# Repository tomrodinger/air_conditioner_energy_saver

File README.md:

# air_conditioner_energy_saver
This are all the open sources for a device that automatically controls your AC unit to turn it on or off

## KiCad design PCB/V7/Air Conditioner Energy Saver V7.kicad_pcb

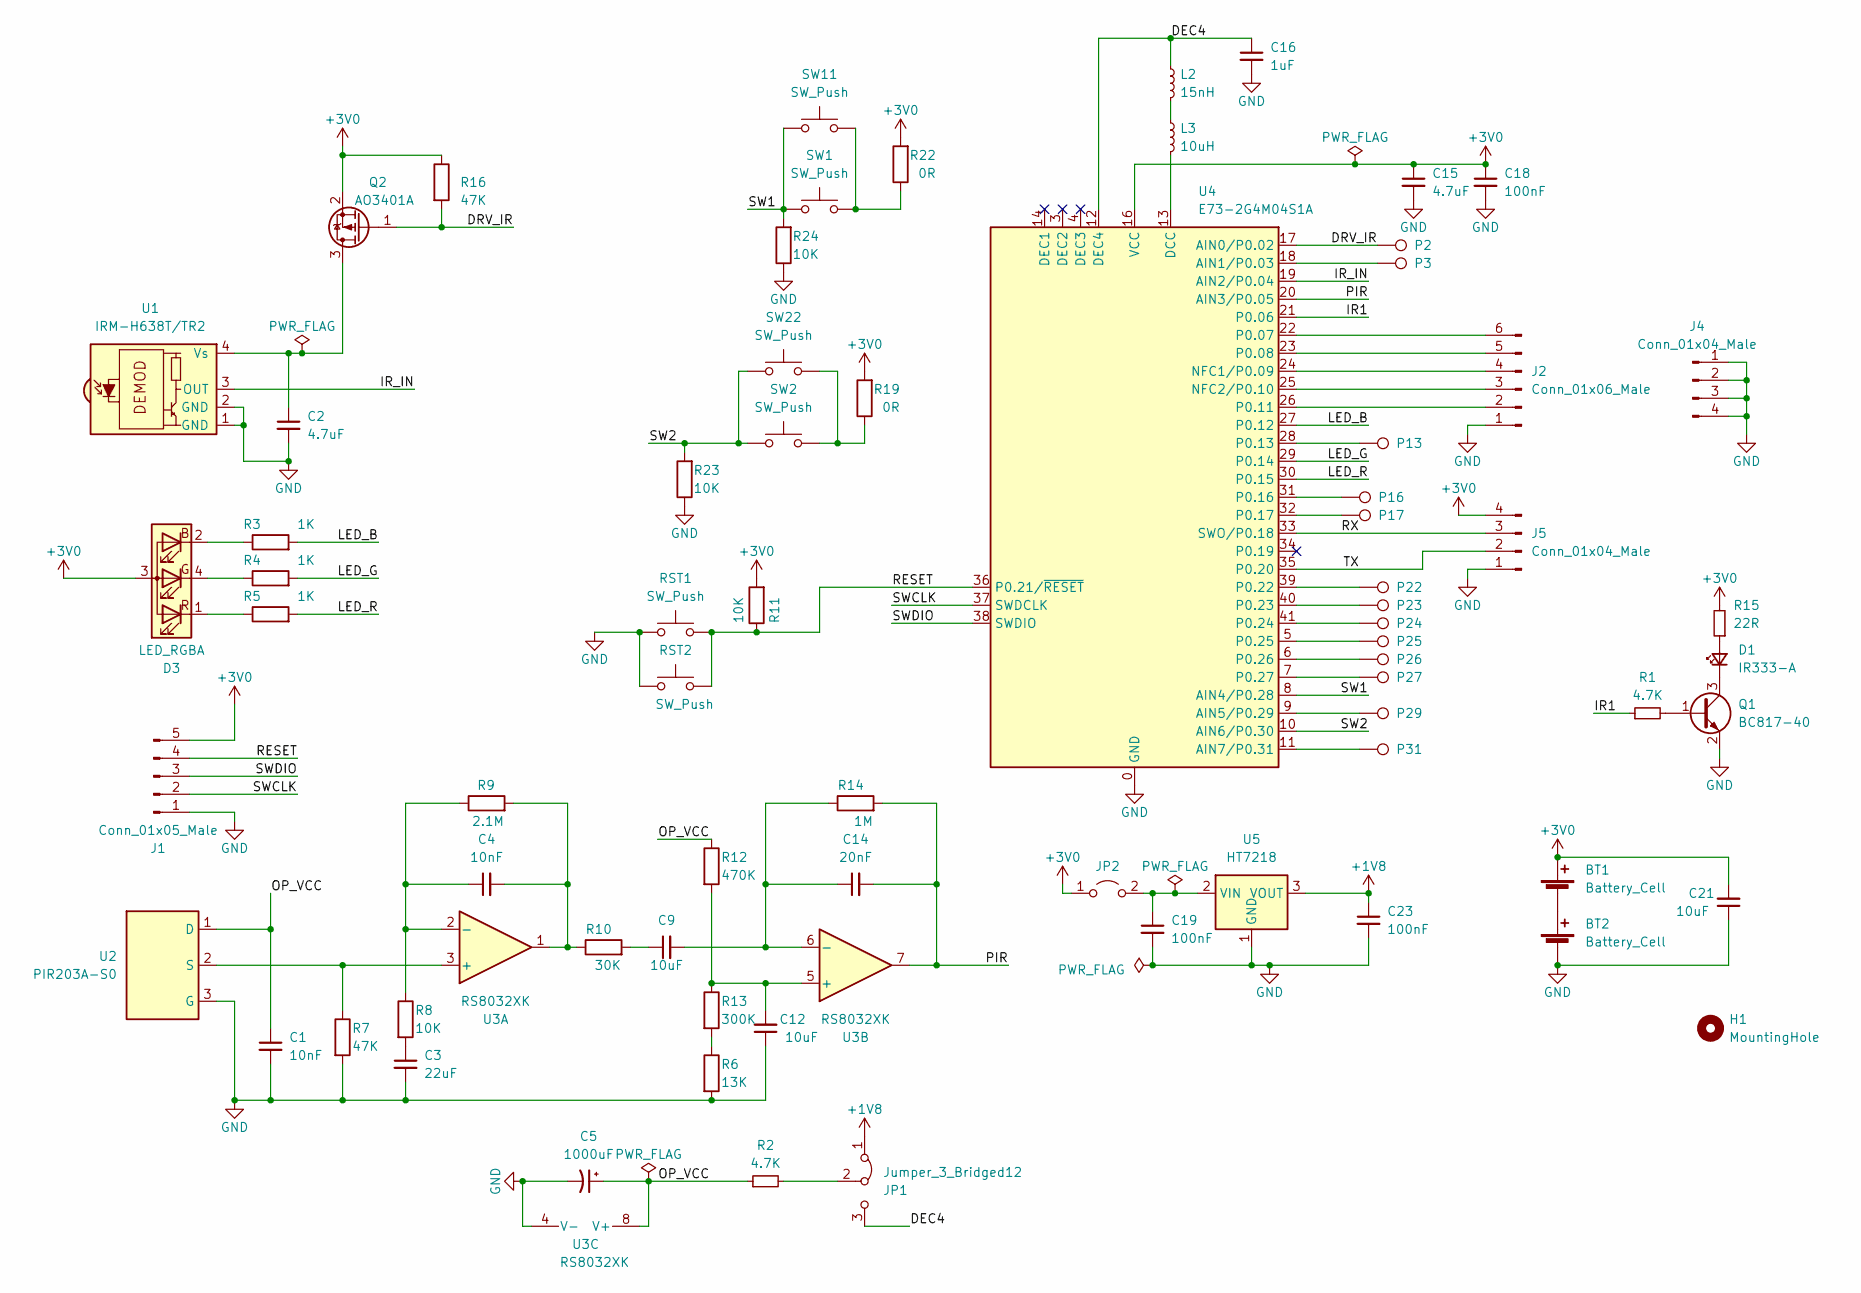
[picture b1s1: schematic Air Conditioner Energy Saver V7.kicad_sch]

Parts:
BT1, BT2: Battery_Cell; AA Batt
C1, C4: 10nF; C_0402_1005Metric; MPN CL05B103KB5NNNC; LCSC C15195
C2: 4.7uF; C_0603_1608Metric; MPN CL10A475KO8NNNC; LCSC C19666
C3: 22uF; C_1206_3216Metric; MPN CL31A226KAHNNNE; LCSC C12891
C5: 1000uF; CP_Elec_8x10.5; MPN RVT1A102M0810; LCSC C99833
C9, C12, C21: 10uF; C_1206_3216Metric; MPN CL31A106KBHNNNE; LCSC C13585
C14: 20nF; C_0603_1608Metric; MPN CC0603KRX7R9BB203; LCSC C282065
C15: 4.7uF; C_0805_2012Metric; MPN CL21A475KAQNNNE; LCSC C1779
C16: 1uF; C_0603_1608Metric; MPN CL10A105KB8NNNC; LCSC C15849
C18, C19, C23: 100nF; C_0402_1005Metric; MPN CL05B104KB54PNC; LCSC C307331
D1: IR333-A; LED_D5.0mm_Horizontal_O3.81mm_Z3.0mm; MPN IR333-A; LCSC C264290
D3: LED_RGBA; FM-B2020RGBA-HG; MPN FM-B2020RGBA-HG; LCSC PN C108793
H1: MountingHole; Mounting Hole 2.3mm
J1: Conn_01x05_Male; PinHeader_1x05_P2.54mm_Vertical; MPN PZ254V-11-05P; LCSC C492404
J2: Conn_01x06_Male; PinHeader_1x06_P2.54mm_Vertical; MPN PZ254V-11-06P; LCSC C492405
J4, J5: Conn_01x04_Male; PinHeader_1x04_P2.54mm_Vertical; MPN PZ254V-11-04P; LCSC C2691448
JP1: Jumper_3_Bridged12; PinHeader_1x03_P2.54mm_Vertical; MPN PZ254V-11-03P; LCSC C2937625
JP2: Jumper_2_Open; TestPoint_2Pads_Pitch2.54mm_Drill0.8mm
L2: 15nH; L_0402_1005Metric; MPN SDCL1005C15NJTDF; LCSC C27143
L3: 10uH; L_0603_1608Metric; MPN SDFL1608S100KTF; LCSC C1035
P2, P3, P13, P16, P17, P22, P23, P24, P25, P26, P27, P29, P31: TestPoint; TestPoint_Pad_1.5x1.5mm
Q1: BC817-40; SOT-23; MPN BC817-40; LCSC PN C85078
Q2: AO3401A; SOT-23; MPN AO3401A; LCSC PN C15127
R1: 4.7K; R_0402_1005Metric; MPN 0402WGF4701TCE; LCSC C25900
R2: 4.7K; R_0603_1608Metric; MPN 0603WAF4701T5E; LCSC C23162
R3, R4, R5: 1K; R_0402_1005Metric; MPN 0402WGF1001TCE; LCSC PN C11702
R6: 13K; R_0402_1005Metric; MPN 0402WGJ0133TCE; LCSC PN C25537
R7, R16: 47K; R_0402_1005Metric; MPN 0402WGF4702TCE; LCSC C25792
R8, R11, R23, R24: 10K; R_0402_1005Metric; MPN 0402WGF1002TCE; LCSC C25744
R9: 2.1M; R_0603_1608Metric; MPN RC0603FR-072M1L; LCSC C482785
R10: 30K; R_0402_1005Metric; MPN RC0402FR-0730KL; LCSC C138008
R12: 470K; R_0402_1005Metric; MPN 0402WGF4703TCE; LCSC PN C25790
R13: 300K; R_0402_1005Metric; MPN 0402WGF3003TCE; LCSC PN C25774
R14: 1M; R_0402_1005Metric; MPN 0402WGF1004TCE; LCSC C26083
R15: 22R; R_0603_1608Metric; MPN 0603WAF220JT5E; LCSC C23345
R19, R22: 0R; R_0402_1005Metric; MPN 0402WGF0000TCE; LCSC C17168
RST1, RST2: SW_Push; SW_SPST_EVQPE1; MPN TS-1088-AR02016; LCSC PN C720477
SW1, SW2, SW11, SW22: SW_Push; SW_SPST_EVQPE1; MPN TS-1088-AR02016; LCSC PN C720477
U1: IRM-H638T/TR2; IRM-H638; MPN IRM-H638T/TR2; LCSC C91447
U2: PIR203A-S0; TO-39-3; MPN PIR203A-S0; LCSC C2887899
U3: RS8032XK; SOIC-8_3.9x4.9mm_P1.27mm; MPN RS8032XK; LCSC C237005
U4: E73-2G4M04S1A; E73-2G4M04S; MPN E73-2G4M04S1B; LCSC C411305
U5: HT7218; SOT-89-3; MPN HT7218; LCSC C259572

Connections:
+1V8: C23.1, JP1.1 (A), U5.3 (VOUT)
+3V0: BT1.1 (+), C15.1, C18.1, C21.2, D3.3 (A), J1.5, J5.4, JP2.1 (A), Q2.2 (S), R11.2, R15.2, R16.1, R19.2, R22.2, U4.16 (VCC)
/DEC4: C16.1, JP1.3 (B), L2.1, U4.12 (DEC4)
/DRV_IR: P2.1, Q2.1 (G), R16.2, U4.17 (AIN0/P0.02)
/IR1: R1.1, U4.21 (P0.06)
/IR_IN: U1.3 (OUT), U4.19 (AIN2/P0.04)
/LED_B: R3.2, U4.27 (P0.12)
/LED_G: R4.2, U4.29 (P0.14)
/LED_R: R5.2, U4.30 (P0.15)
/OP_VCC: C1.1, C5.1, R2.1, R12.1, U2.1 (D), U3.8 (V+)
/PIR: C14.2, R14.2, U3.7, U4.20 (AIN3/P0.05)
/RESET: J1.4, R11.1, RST1.2, RST2.2, U4.36 (P0.21/~RESET)
/RX: J5.3, U4.33 (SWO/P0.18)
/SW1: R24.2, SW1.1, SW11.1, U4.8 (AIN4/P0.28)
/SW2: R23.2, SW2.1, SW22.1, U4.10 (AIN6/P0.30)
/SWCLK: J1.2, U4.37 (SWDCLK)
/SWDIO: J1.3, U4.38 (SWDIO)
/TX: J5.2, U4.35 (P0.20)
GND: BT2.2 (-), C1.2, C2.2, C3.2, C5.2, C12.1, C15.2, C16.2, C18.2, C19.2, C21.1, C23.2, J1.1, J2.1, J4.1, J4.2, J4.3, J4.4, J5.1, Q1.2 (E), R6.2, R7.2, R23.1, R24.1, RST1.1, RST2.1, U1.1 (GND), U1.2 (GND), U2.3 (G), U3.4 (V-), U4.0 (GND), U4.1 (GND), U4.2 (GND), U4.15 (GND), U4.42 (GND), U4.43 (GND), U5.1 (GND)
unnamed: BT1.2 (-), BT2.1 (+)
unnamed: C2.1, Q2.3 (D), U1.4 (Vs)
unnamed: C3.1, R8.2
unnamed: C4.1, R8.1, R9.1, U3.2 (-)
unnamed: C4.2, R9.2, R10.1, U3.1
unnamed: C9.1, R10.2
unnamed: C12.2, R12.2, R13.1, U3.5 (+)
unnamed: C9.2, C14.1, R14.1, U3.6 (-)
unnamed: C19.1, JP2.2 (B), U5.2 (VIN)
unnamed: D1.1 (K), Q1.3 (C)
unnamed: D1.2 (A), R15.1
unnamed: D3.1 (RK), R5.1
unnamed: D3.2 (BK), R3.1
unnamed: D3.4 (GK), R4.1
unnamed: J2.2, U4.26 (P0.11)
unnamed: J2.3, U4.25 (NFC2/P0.10)
unnamed: J2.4, U4.24 (NFC1/P0.09)
unnamed: J2.5, U4.23 (P0.08)
unnamed: J2.6, U4.22 (P0.07)
unnamed: JP1.2 (C), R2.2
unnamed: L2.2, L3.1
unnamed: L3.2, U4.13 (DCC)
unnamed: P3.1, U4.18 (AIN1/P0.03)
unnamed: P13.1, U4.28 (P0.13)
unnamed: P16.1, U4.31 (P0.16)
unnamed: P17.1, U4.32 (P0.17)
unnamed: P22.1, U4.39 (P0.22)
unnamed: P23.1, U4.40 (P0.23)
unnamed: P24.1, U4.41 (P0.24)
unnamed: P25.1, U4.5 (P0.25)
unnamed: P26.1, U4.6 (P0.26)
unnamed: P27.1, U4.7 (P0.27)
unnamed: P29.1, U4.9 (AIN5/P0.29)
unnamed: P31.1, U4.11 (AIN7/P0.31)
unnamed: Q1.1 (B), R1.2
unnamed: R7.1, U2.2 (S), U3.3 (+)
unnamed: R6.1, R13.2
unnamed: R19.1, SW2.2, SW22.2
unnamed: R22.1, SW1.2, SW11.2

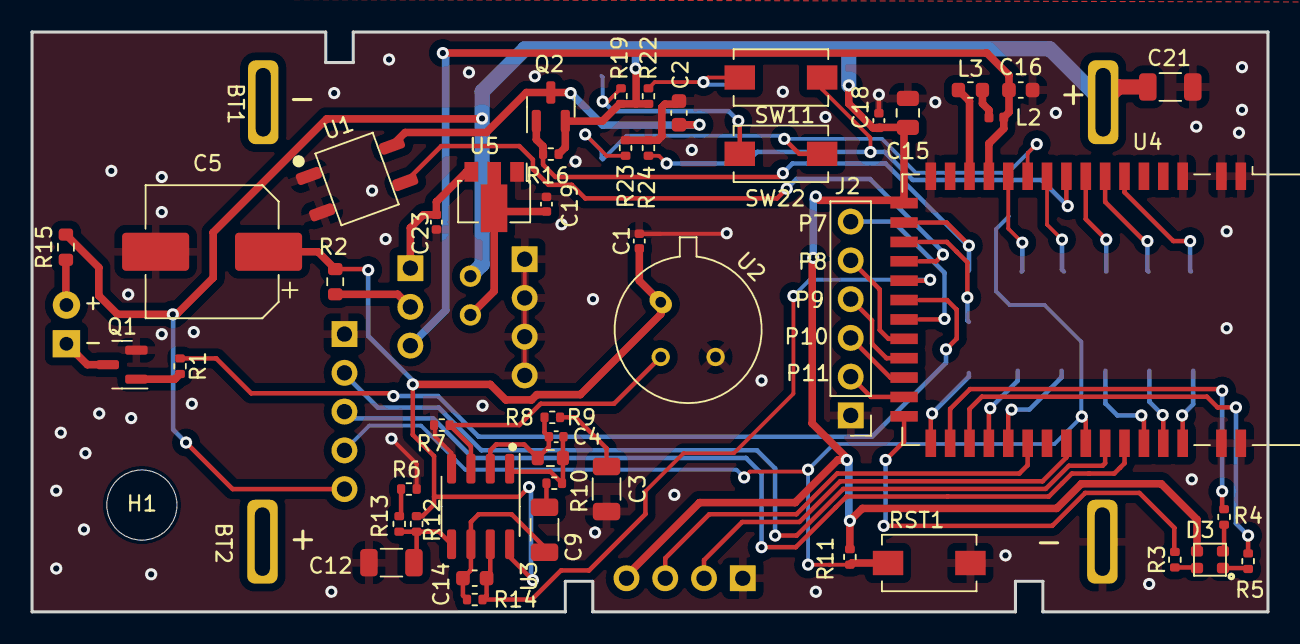
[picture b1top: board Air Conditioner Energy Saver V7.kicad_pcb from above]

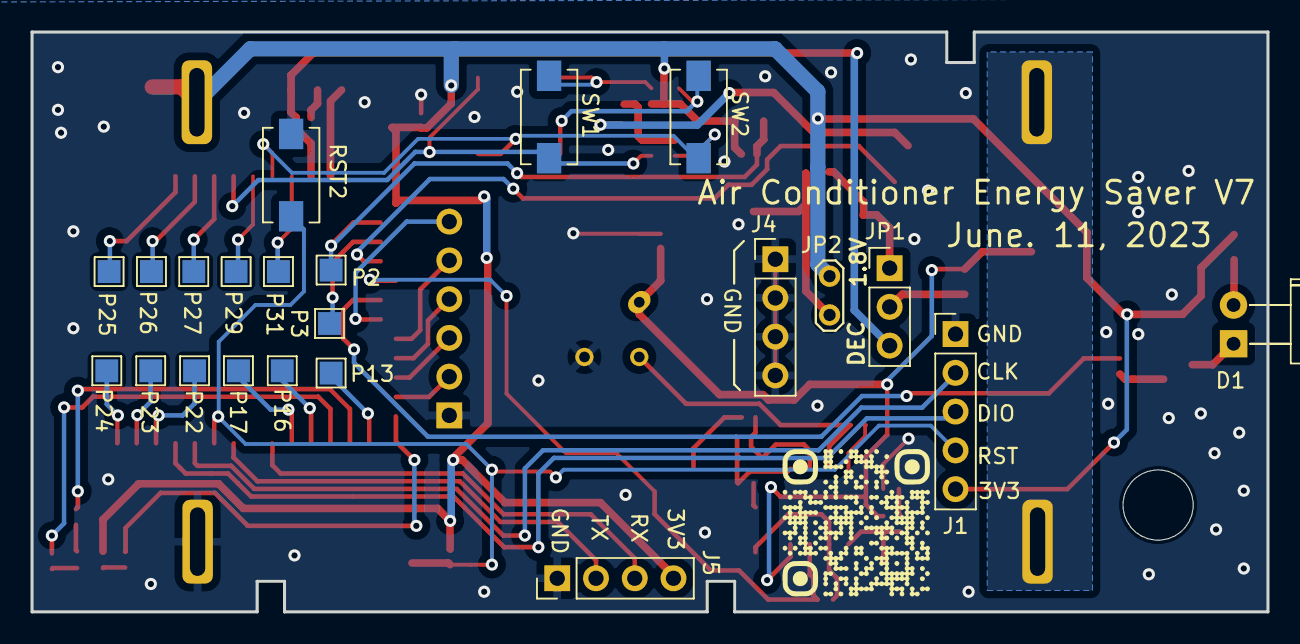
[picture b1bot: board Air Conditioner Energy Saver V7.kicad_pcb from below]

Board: 2 copper layers, 81.0 x 38.0 mm, 73 parts (22 on the bottom side), 58 nets.

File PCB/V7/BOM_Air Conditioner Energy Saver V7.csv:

Source:,G:\OneDrive\Work\Upwork\TomRodinger\Air Conditioner Energy Saver V7\Air Conditioner Energy Saver V7.kicad_sch,,,,,,,,,,,,
Date:,6/16/2023 9:33,,,,,,,,,,,,
Tool:,Eeschema 7.0.1,,,,,,,,,,,,
Generator:,C:\Program Files\KiCad\7.0\bin\scripting\plugins/bom_csv_grouped_by_value.py,,,,,,,,,,,,
Component Count:,73,,,,,,,,,,,,
,,,,,,,,,,,,,
Collated Components:,,,,,,,,,,,,,
,,,,,,,,,,,,,
Item,Qty,Reference(s),Value,LibPart,Footprint,Datasheet,DNP,Description,LCSC,LCSC ,LCSC PN,MN,MPN
1,2,"BT1, BT2",Battery_Cell,Device:Battery_Cell,Motion_sense:AA Batt,~,,Battery_Cell,,,,,
2,2,"C1, C4",10nF,Device:C_Small,Capacitor_SMD:C_0402_1005Metric,~,,50V 10nF X7R ±10% 0402 Multilayer Ceramic Capacitors,C15195,,,Samsung Electro-Mechanics,CL05B103KB5NNNC
3,1,C2,4.7uF,Device:C_Small,Capacitor_SMD:C_0603_1608Metric,~,,16V 4.7uF X5R ±10% 0603 Multilayer Ceramic,C19666,,,Samsung Electro-Mechanics,CL10A475KO8NNNC
4,1,C3,22uF,Device:C_Small,Capacitor_SMD:C_1206_3216Metric,~,,25V 22uF X5R ±10% 1206 Multilayer Ceramic Capacitors,C12891,,,Samsung Electro-Mechanics,CL31A226KAHNNNE
5,1,C5,1000uF,Device:C_Polarized_Small_US,Capacitor_SMD:CP_Elec_8x10.5,~,,"1000uF 10V ±20% SMD,D8xL10.2mm ",C99833,,,ROQANG,RVT1A102M0810
6,3,"C9, C12, C21",10uF,Device:C_Small,Capacitor_SMD:C_1206_3216Metric,~,,50V 10uF X5R ±10% 1206 Multilayer Ceramic ,C13585,,,Samsung Electro-Mechanics,CL31A106KBHNNNE
7,1,C14,20nF,Device:C_Small,Capacitor_SMD:C_0603_1608Metric,~,,CAP CER 0.02UF 50V X7R 0603,C282065,,,YAGEO,CC0603KRX7R9BB203
8,1,C15,4.7uF,Device:C_Small,Capacitor_SMD:C_0805_2012Metric,~,,25V 4.7uF X5R ±10% 0805 Multilayer Ceramic,C1779,,,Samsung Electro-Mechanics,CL21A475KAQNNNE
9,1,C16,1uF,Device:C_Small,Capacitor_SMD:C_0603_1608Metric,~,,50V 1uF X5R ±10% 0603 Multilayer Ceramic Capacitors,C15849,,,Samsung Electro-Mechanics,CL10A105KB8NNNC
10,3,"C18, C19, C23",100nF,Device:C_Small,Capacitor_SMD:C_0402_1005Metric,~,,50V 100nF X7R ±10% 0402 Multilayer Ceramic Capacitors,C307331,,,Samsung Electro-Mechanics,CL05B104KB54PNC
11,1,D1,IR333-A,Device:LED_Small,LED_THT:LED_D5.0mm_Horizontal_O3.81mm_Z3.0mm,~,,EMITTER IR 940NM 100MA RADIAL,C264290,,,Everlight Elec,IR333-A
12,1,D3,LED_RGBA,Device:LED_RGBA,Motion_sense:FM-B2020RGBA-HG,~,,"RGB SMD,2.1x2.1mm Light Emitting Diodes """,C108793,,C108793,Foshan NationStar Optoelectronics,FM-B2020RGBA-HG
13,1,H1,MountingHole,Mechanical:MountingHole,Motion_sense:Mounting Hole 2.3mm,~,,MountingHole,,,,,
14,1,J1,Conn_01x05_Male,Connector:Conn_01x05_Male,Connector_PinHeader_2.54mm:PinHeader_1x05_P2.54mm_Vertical,~,,2.54mm Plugin Black Brass 1x5P Plugin,C492404,,,XFCN,PZ254V-11-05P
15,1,J2,Conn_01x06_Male,Connector:Conn_01x06_Male,Connector_PinHeader_2.54mm:PinHeader_1x06_P2.54mm_Vertical,~,,2.54mm Plugin Black Brass 1x6P Plugin,C492405,,,XFCN,PZ254V-11-06P
16,2,"J4, J5",Conn_01x04_Male,Connector:Conn_01x04_Male,Connector_PinHeader_2.54mm:PinHeader_1x04_P2.54mm_Vertical,~,,2.54mm Plugin Black 1x4P Plugin,C2691448,,,XFCN,PZ254V-11-04P
17,1,JP1,Jumper_3_Bridged12,Jumper:Jumper_3_Bridged12,Connector_PinHeader_2.54mm:PinHeader_1x03_P2.54mm_Vertical,~,,2.54mm Plugin Black 1x3P Plugin,C2937625,,,XFCN,PZ254V-11-03P
18,1,JP2,Jumper_2_Open,Jumper:Jumper_2_Open,TestPoint:TestPoint_2Pads_Pitch2.54mm_Drill0.8mm,~,,,,,,,
19,1,L2,15nH,Device:L_Small,Inductor_SMD:L_0402_1005Metric,~,,300mA 15nH ±5% 500mΩ 0402 Inductors (SMD) ROHS,C27143,,,Sunlord,SDCL1005C15NJTDF
20,1,L3,10uH,Device:L_Small,Inductor_SMD:L_0603_1608Metric,~,,3mA 10uH ±10% 1.85Ω 0603 Inductors (SMD) ROHS,C1035,,,Sunlord,SDFL1608S100KTF
21,13,"P2, P3, P13, P16, P17, P22, P23, P24, P25, P26, P27, P29, P31",TestPoint,Connector:TestPoint,TestPoint:TestPoint_Pad_1.5x1.5mm,~,,TestPoint,,,,,
22,1,Q1,BC817-40,Transistor_BJT:BC817,Package_TO_SOT_SMD:SOT-23,https://www.onsemi.com/pub/Collateral/BC818-D.pdf,,45V 250mW 500mA NPN SOT-23 ,C85078,,C85078,ST(Semtech),BC817-40
23,1,Q2,AO3401A,Transistor_FET:AO3401A,Package_TO_SOT_SMD:SOT-23,http://www.aosmd.com/pdfs/datasheet/AO3401A.pdf,,"30V 4A 44mΩ@10V,4.3A 1.4W P Channel SOT-23",C15127,,C15127,Alpha & Omega Semicon,AO3401A
24,1,R1,4.7K,Device:R_Small,Resistor_SMD:R_0402_1005Metric,~,,62.5mW Thick Film Resistors ±1% 4.7kΩ 0402  Chip Resistor - Surface Mount ROHS,C25900,,,UNI-ROYAL(Uniroyal Elec),0402WGF4701TCE
25,1,R2,4.7K,Device:R_Small,Resistor_SMD:R_0603_1608Metric,~,,100mW Thick Film Resistors ±1% 4.7kΩ 0603  Chip Resistor - Surface Mount ROHS,C23162,,,UNI-ROYAL(Uniroyal Elec),0603WAF4701T5E
26,3,"R3, R4, R5",1K,Device:R,Resistor_SMD:R_0402_1005Metric,~,,Resistors ±100ppm/℃ ±1% 1kΩ 0402,C11702,,C11702,UNI-ROYAL(Uniroyal Elec),0402WGF1001TCE
27,1,R6,13K,Device:R,Resistor_SMD:R_0402_1005Metric,~,,Resistors ±100ppm/℃ ±5% 13kΩ 0402,C25537,,C25537,UNI-ROYAL(Uniroyal Elec),0402WGJ0133TCE
28,2,"R7, R16",47K,Device:R,Resistor_SMD:R_0402_1005Metric,~,,62.5mW Thick Film Resistors ±1% 47kΩ 0402  Chip Resistor - Surface Mount ROHS,C25792,,,UNI-ROYAL(Uniroyal Elec),0402WGF4702TCE
29,4,"R8, R11, R23, R24",10K,Device:R,Resistor_SMD:R_0402_1005Metric,~,,62.5mW Thick Film Resistors ±100ppm/℃ ±1% 10kΩ 0402  Chip Resistor - Surface Mount ROHS,C25744,,,UNI-ROYAL(Uniroyal Elec),0402WGF1002TCE
30,1,R9,2.1M,Device:R,Resistor_SMD:R_0603_1608Metric,~,,Resistors ±100ppm/℃ ±1% 2.1MΩ 0603,C482785,,,YAGEO,RC0603FR-072M1L
31,1,R10,30K,Device:R,Resistor_SMD:R_0402_1005Metric,~,,RES 30K OHM 1% 1/16W 0402,C138008,,,YAGEO,RC0402FR-0730KL
32,1,R12,470K,Device:R,Resistor_SMD:R_0402_1005Metric,~,,Resistors ±100ppm/℃ ±1% 470kΩ 0402,C25790,,C25790,UNI-ROYAL(Uniroyal Elec),0402WGF4703TCE
33,1,R13,300K,Device:R,Resistor_SMD:R_0402_1005Metric,~,,Resistors ±100ppm/℃ ±1% 470kΩ 0402,C25774,,C25774,UNI-ROYAL(Uniroyal Elec),0402WGF3003TCE
34,1,R14,1M,Device:R,Resistor_SMD:R_0402_1005Metric,~,,62.5mW Thick Film Resistors ±100ppm/℃ ±1% 1MΩ 0402  Chip Resistor - Surface Mount ROHS,C26083,,,UNI-ROYAL(Uniroyal Elec),0402WGF1004TCE
35,1,R15,22R,Device:R_Small,Resistor_SMD:R_0603_1608Metric,~,,100mW Thick Film Resistors ±1% 22Ω 0603  Chip Resistor - Surface Mount ROHS,C23345,,,UNI-ROYAL(Uniroyal Elec),0603WAF220JT5E
36,2,"R19, R22",0R,Device:R,Resistor_SMD:R_0402_1005Metric,~,,62.5mW Thick Film Resistors ±800ppm/℃ ±1% 0Ω 0402 Chip Resistor - Surface Mount ROHS,C17168,,,UNI-ROYAL(Uniroyal Elec),0402WGF0000TCE
37,6,"RST1, RST2, SW1, SW2, SW11, SW22",SW_Push,Switch:SW_Push,Button_Switch_SMD:SW_SPST_EVQPE1,~,,SPST SMD Tactile Switches,C720477,,C720477,XUNPU,TS-1088-AR02016
38,1,U1,IRM-H638T/TR2,Interface_Optical:TSOP23xx,Motion_sense:IRM-H638,,,SENSOR REMOTE REC 38.0KHZ 8M,C91447,,,Everlight Elec,IRM-H638T/TR2
39,1,U2,PIR203A-S0,Sensor_Magnetic:A1101ELHL,Package_TO_SOT_THT:TO-39-3,,,TO-52-3 Human Body Sensing Sensor,C2887899,,,NEWOPTO,PIR203A-S0
40,1,U3,RS8032XK,Amplifier_Operational:LM358,Package_SO:SOIC-8_3.9x4.9mm_P1.27mm,http://www.ti.com/lit/ds/symlink/lm2904-n.pdf,,SOP-8 Operational Amplifier,C237005,C237005,,Jiangsu RUNIC Tech,RS8032XK
41,1,U4,E73-2G4M04S1A,RF_Module:E73-2G4M04S-52810,RF_Module:E73-2G4M04S,http://www.cdebyte.com/en/downpdf.aspx?id=243,,Bluetooth Modules,C411305,,,Chengdu Ebyte Elec Tech,E73-2G4M04S1B
42,1,U5,HT7218,Regulator_Linear:HT75xx-1-SOT89,Package_TO_SOT_SMD:SOT-89-3,https://www.holtek.com/documents/10179/116711/HT75xx-1v250.pdf,,300mA Fixed 1.8V~1.8V Positive 8V SOT-89-3,C259572,,,Holtek Semicon,HT7218

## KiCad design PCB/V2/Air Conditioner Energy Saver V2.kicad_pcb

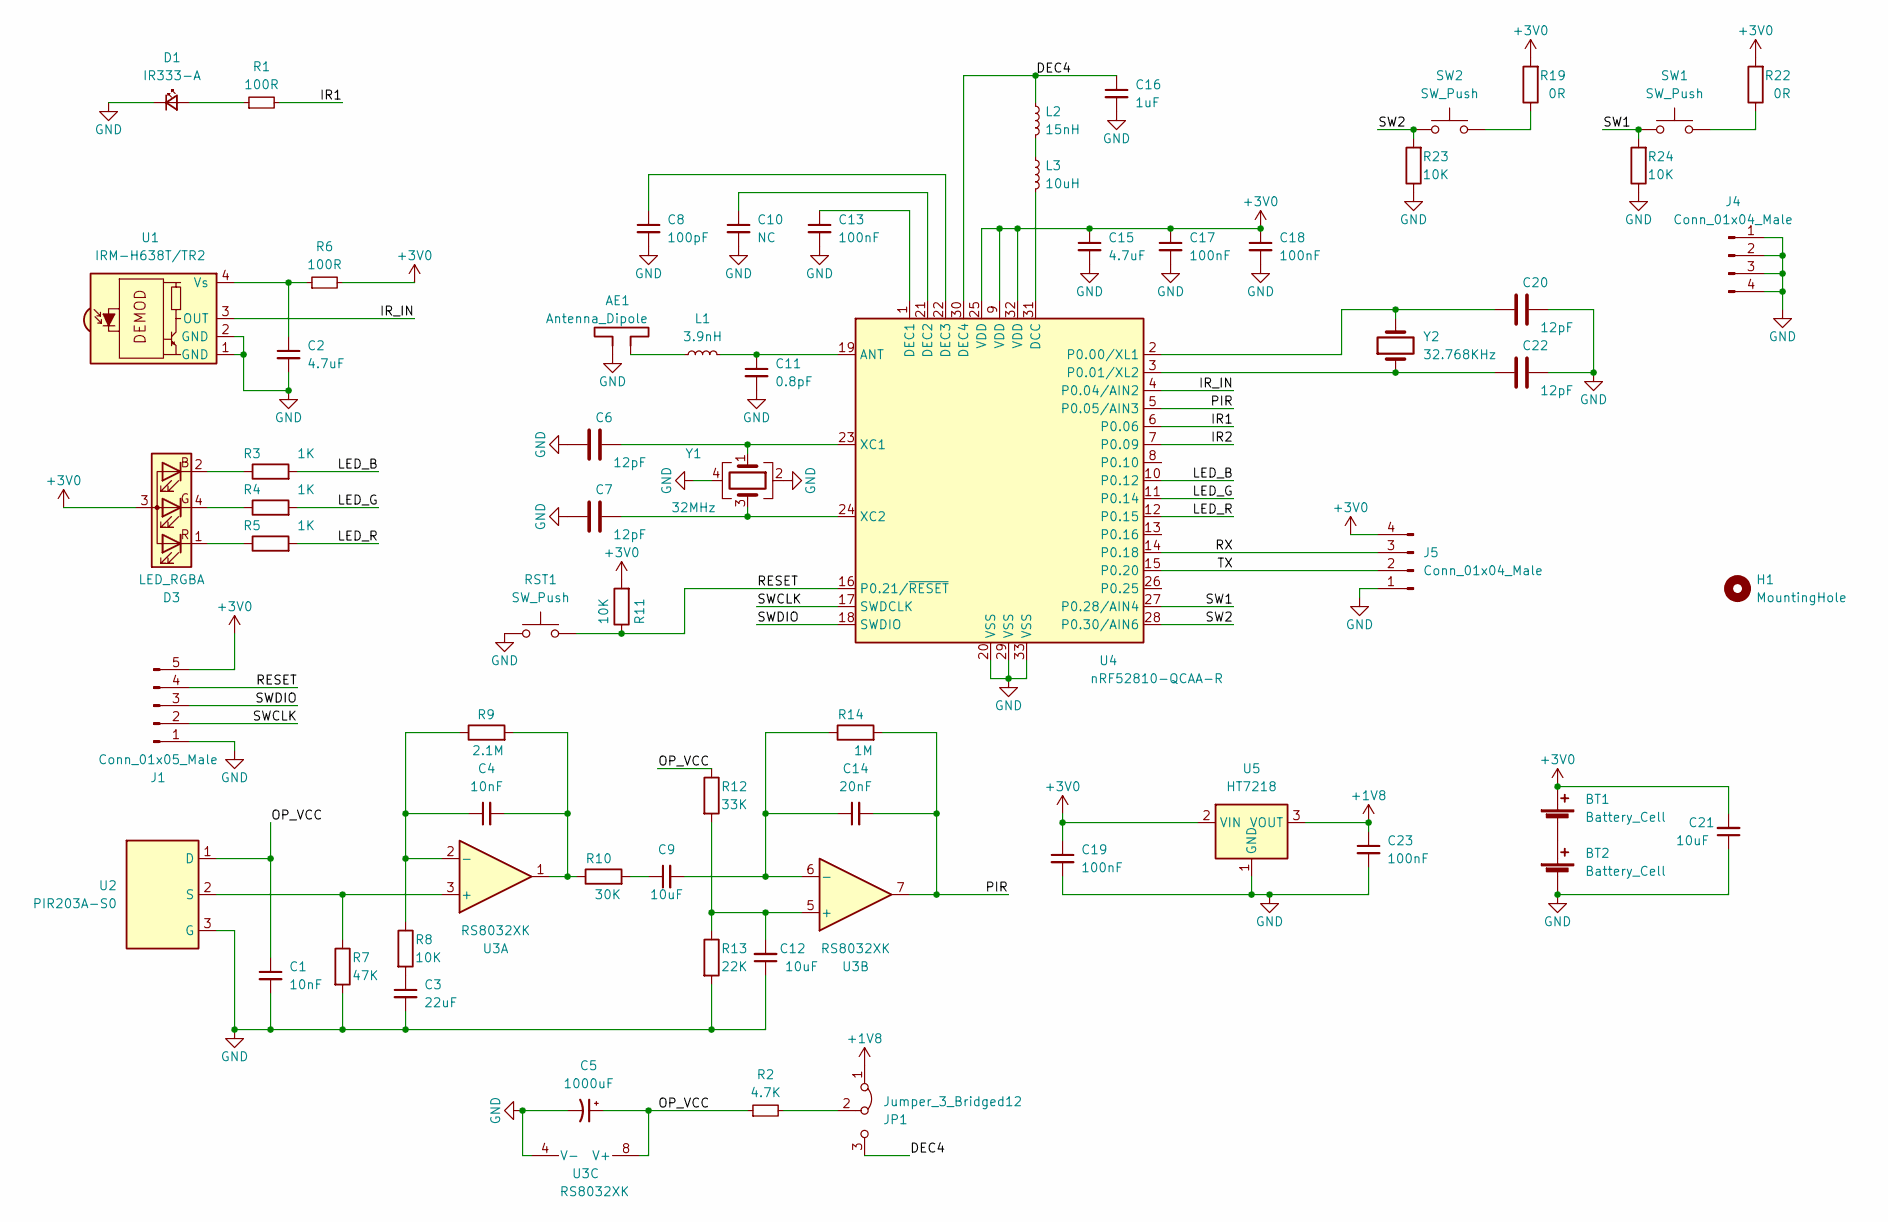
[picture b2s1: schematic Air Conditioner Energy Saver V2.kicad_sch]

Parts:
AE1: Antenna_Dipole; Texas_SWRA117D_2.4GHz_Right
BT1, BT2: Battery_Cell; AA Batt
C1, C4: 10nF; C_0402_1005Metric
C2: 4.7uF; C_0603_1608Metric
C3: 22uF; C_1206_3216Metric
C5: 1000uF; CP_Elec_8x10.5; LCSC C99833
C6, C20: 12pF; C_0402_1005Metric; LCSC PN C1547
C7, C22: 12pF; C_0402_1005Metric
C8: 100pF; C_0402_1005Metric
C9, C12, C21: 10uF; C_1206_3216Metric
C10: NC; C_0402_1005Metric
C11: 0.8pF; C_0402_1005Metric
C13, C17, C18, C19, C23: 100nF; C_0402_1005Metric
C14: 20nF; C_0603_1608Metric
C15: 4.7uF; C_0805_2012Metric
C16: 1uF; C_0603_1608Metric
D1: IR333-A; LED_D5.0mm; LCSC C264290
D3: LED_RGBA; FM-B2020RGBA-HG; LCSC PN C108793
H1: MountingHole; Mounting Hole 2.3mm
J1: Conn_01x05_Male; PinHeader_1x05_P2.54mm_Vertical
J4, J5: Conn_01x04_Male; PinHeader_1x04_P2.54mm_Vertical
JP1: Jumper_3_Bridged12; PinHeader_1x03_P2.54mm_Vertical
L1: 3.9nH; L_0402_1005Metric
L2: 15nH; L_0402_1005Metric
L3: 10uH; L_0603_1608Metric
R1, R6: 100R; R_0603_1608Metric
R2: 4.7K; R_0603_1608Metric
R3, R4, R5: 1K; R_0402_1005Metric; LCSC PN C11702
R7: 47K; R_0402_1005Metric
R8, R11, R23, R24: 10K; R_0402_1005Metric
R9: 2.1M; R_0603_1608Metric
R10: 30K; R_0402_1005Metric
R12: 33K; R_0402_1005Metric
R13: 22K; R_0402_1005Metric
R14: 1M; R_0402_1005Metric
R19, R22: 0R; R_0402_1005Metric
RST1: SW_Push; SW_SPST_EVQPE1; LCSC PN C720477
SW1, SW2: SW_Push; SW_SPST_EVQPE1; LCSC PN C720477
U1: IRM-H638T/TR2; IRM-H638; LCSC C91447
U2: PIR203A-S0; TO-39-3; LCSC C2887899
U3: RS8032XK; SOIC-8_3.9x4.9mm_P1.27mm; LCSC C237005
U4: nRF52810-QCAA-R; QFN-32-1EP_5x5mm_P0.5mm_EP3.6x3.6mm; LCSC C519278
U5: HT7218; SOT-89-3; LCSC C259233
Y1: 32MHz; Crystal_SMD_2016-4Pin_2.0x1.6mm; LCSC PN C255896
Y2: 32.768KHz; Crystal_SMD_3215-2Pin_3.2x1.5mm; LCSC C32346

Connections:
+1V8: C23.1, JP1.1 (A), U5.3 (VOUT)
+3V0: BT1.1 (+), C15.1, C17.1, C18.1, C19.1, C21.2, D3.3 (A), J1.5, J5.4, R6.2, R11.2, R19.2, R22.2, U4.9 (VDD), U4.25 (VDD), U4.32 (VDD), U5.2 (VIN)
/DEC4: C16.1, JP1.3 (B), L2.1, U4.30 (DEC4)
/IR1: R1.2, U4.6 (P0.06)
/IR2: U4.7 (P0.09)
/IR_IN: U1.3 (OUT), U4.4 (P0.04/AIN2)
/LED_B: R3.2, U4.10 (P0.12)
/LED_G: R4.2, U4.11 (P0.14)
/LED_R: R5.2, U4.12 (P0.15)
/OP_VCC: C1.1, C5.1, R2.1, R12.1, U2.1 (D), U3.8 (V+)
/PIR: C14.2, R14.2, U3.7, U4.5 (P0.05/AIN3)
/RESET: J1.4, R11.1, RST1.2, U4.16 (P0.21/~RESET)
/RX: J5.3, U4.14 (P0.18)
/SW1: R24.2, SW1.1, U4.27 (P0.28/AIN4)
/SW2: R23.2, SW2.1, U4.28 (P0.30/AIN6)
/SWCLK: J1.2, U4.17 (SWDCLK)
/SWDIO: J1.3, U4.18 (SWDIO)
/TX: J5.2, U4.15 (P0.20)
GND: AE1.2, BT2.2 (-), C1.2, C2.2, C3.2, C5.2, C6.2, C7.2, C8.2, C10.2, C11.2, C12.1, C13.2, C15.2, C16.2, C17.2, C18.2, C19.2, C20.1, C21.1, C22.1, C23.2, D1.1 (K), J1.1, J4.1, J4.2, J4.3, J4.4, J5.1, R7.2, R13.2, R23.1, R24.1, RST1.1, U1.1 (GND), U1.2 (GND), U2.3 (G), U3.4 (V-), U4.20 (VSS), U4.29 (VSS), U4.33 (VSS), U5.1 (GND), Y1.2, Y1.4
unnamed: AE1.1, L1.1
unnamed: BT1.2 (-), BT2.1 (+)
unnamed: C2.1, R6.1, U1.4 (Vs)
unnamed: C3.1, R8.2
unnamed: C4.1, R8.1, R9.1, U3.2 (-)
unnamed: C4.2, R9.2, R10.1, U3.1
unnamed: C6.1, U4.23 (XC1), Y1.1
unnamed: C7.1, U4.24 (XC2), Y1.3
unnamed: C8.1, U4.22 (DEC3)
unnamed: C9.1, R10.2
unnamed: C10.1, U4.21 (DEC2)
unnamed: C11.1, L1.2, U4.19 (ANT)
unnamed: C12.2, R12.2, R13.1, U3.5 (+)
unnamed: C13.1, U4.1 (DEC1)
unnamed: C9.2, C14.1, R14.1, U3.6 (-)
unnamed: C20.2, U4.2 (P0.00/XL1), Y2.2
unnamed: C22.2, U4.3 (P0.01/XL2), Y2.1
unnamed: D1.2 (A), R1.1
unnamed: D3.1 (RK), R5.1
unnamed: D3.2 (BK), R3.1
unnamed: D3.4 (GK), R4.1
unnamed: JP1.2 (C), R2.2
unnamed: L2.2, L3.1
unnamed: L3.2, U4.31 (DCC)
unnamed: R7.1, U2.2 (S), U3.3 (+)
unnamed: R19.1, SW2.2
unnamed: R22.1, SW1.2

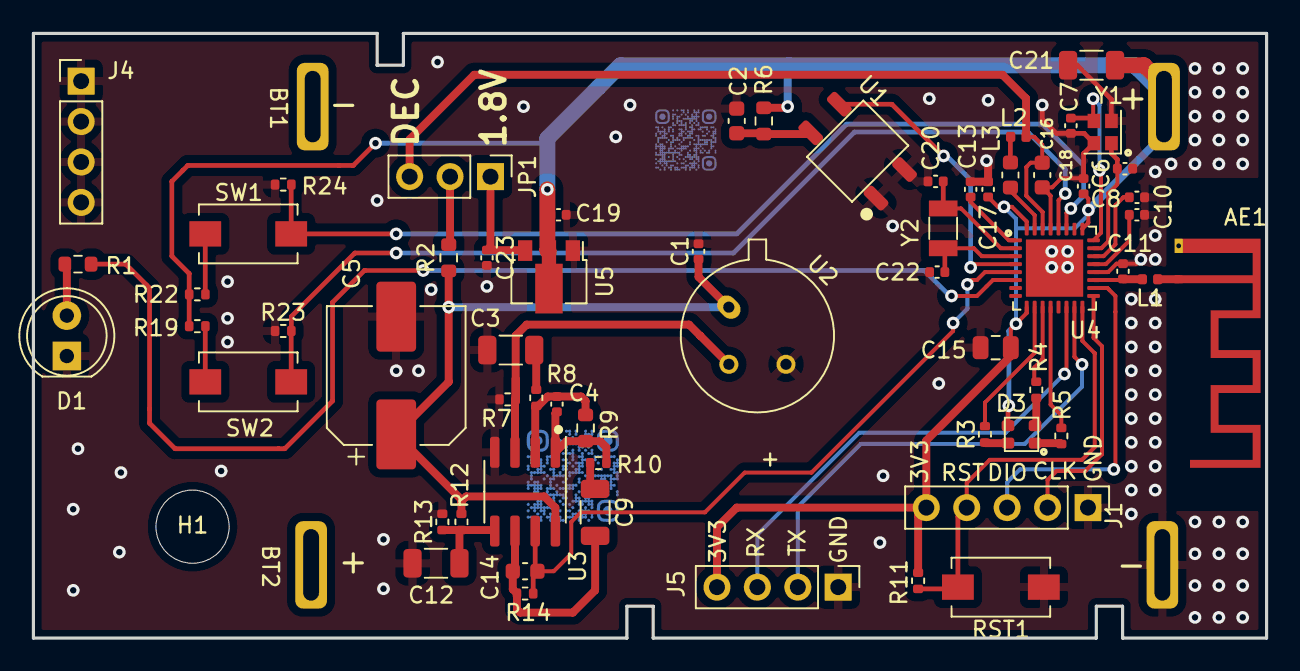
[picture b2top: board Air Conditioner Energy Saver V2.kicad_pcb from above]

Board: 2 copper layers, 77.5 x 38.0 mm, 64 parts (0 on the bottom side), 45 nets.

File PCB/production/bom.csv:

Designator,Footprint,Quantity,Value,LCSC Part #
"BT1, BT2",AA Batt,2,Battery_Cell,
"C1, C4",C_0402_1005Metric,2,10nF,
"C12, C21, C9",C_1206_3216Metric,3,10uF,
C14,C_0603_1608Metric,1,20nF,
C15,C_0805_2012Metric,1,4.7uF,
C16,C_0603_1608Metric,1,1uF,
"C18, C19, C23",C_0402_1005Metric,3,100nF,
C2,C_0603_1608Metric,1,4.7uF,
C3,C_1206_3216Metric,1,22uF,
C5,CP_Elec_8x10.5,1,1000uF,C99833
D1,LED_D5.0mm_Horizontal_O3.81mm_Z3.0mm,1,IR333-A,C264290
D3,FM-B2020RGBA-HG,1,LED_RGBA,
H1,Mounting Hole 2.3mm,1,MountingHole,
J1,PinHeader_1x05_P2.54mm_Vertical,1,Conn_01x05_Male,
J2,PinHeader_1x06_P2.54mm_Vertical,1,Conn_01x06_Male,
"J4, J5",PinHeader_1x04_P2.54mm_Vertical,2,Conn_01x04_Male,
JP1,PinHeader_1x03_P2.54mm_Vertical,1,Jumper_3_Bridged12,
JP2,TestPoint_2Pads_Pitch2.54mm_Drill0.8mm,1,Jumper_2_Open,
L2,L_0402_1005Metric,1,15nH,
L3,L_0603_1608Metric,1,10uH,
"P13, P16, P17, P2, P22, P23, P24, P25, P26, P27, P29, P3, P31",TestPoint_Pad_1.5x1.5mm,13,TestPoint,
Q1,SOT-23,1,BC817-40,
Q2,SOT-23,1,AO3401A,
R1,R_0402_1005Metric,1,4.7K,
R10,R_0402_1005Metric,1,30K,
"R11, R23, R24, R8",R_0402_1005Metric,4,10K,
R12,R_0402_1005Metric,1,470K,
R13,R_0402_1005Metric,1,300K,
R14,R_0402_1005Metric,1,1M,
R15,R_0603_1608Metric,1,22R,
"R16, R7",R_0402_1005Metric,2,47K,
"R19, R22",R_0402_1005Metric,2,0R,
R2,R_0603_1608Metric,1,4.7K,
"R3, R4, R5",R_0402_1005Metric,3,1K,
R6,R_0402_1005Metric,1,13K,
R9,R_0603_1608Metric,1,2.1M,
"RST1, RST2, SW1, SW11, SW2, SW22",SW_SPST_EVQPE1,6,SW_Push,
U1,IRM-H638,1,IRM-H638T/TR2,C91447
U2,TO-39-3,1,PIR203A-S0,C2887899
U3,SOIC-8_3.9x4.9mm_P1.27mm,1,RS8032XK,C237005
U4,E73-2G4M04S,1,E73-2G4M04S-52810,
U5,SOT-89-3,1,HT7218,C259233

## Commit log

2022-10-22 Initial commit of the firmware along with the essential parts of the toolchain to build it.
2022-10-22 Here are the PCB source files for version 1 of the PCB
2022-10-23 adding one .gitignore to avoid checking in the very large entire toolchain
2022-11-07 Adding support for more programmers in the Makefile Adding the ability to transmit and receive Bluetooth advertisement packets using the radio.
2022-11-07 V3 PCB design files
2022-12-08 Implementing the ability for a master and slave device to interchange data in a coordinated way while speeling most of the itme. Refactoring the clock initialization code. Attempting to make interrup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
2022-12-11 Adding missing libraries hidden by .gitignore
2022-12-20 [ble] Adding BLE support
2022-12-20 [ble] Adding S112 softdevice image file
2022-12-29 [pwr] Implemented power modes. Code cleanup
2023-02-10 [make] Implemented platform independent makefile for build
2023-02-11 Adding a function to put the system in system off state to get as low power as possible
2023-02-11 [make] Adding makefile definition files
2023-02-11 [make] Adding needed include files
2023-02-12 Removing all the stuff in .gitignore because it was causing things that we need not to be checked in
2023-02-13 [pwr] Adding system off to the hardware tests
2023-02-14 [pwr] Make sure Softdevice is enabled before requesting system off
2023-04-10 Putting V2 PCB files in the right place
2023-04-10 Ac energy saver V5
2023-04-10 Putting V5 PCB files into the right place.
2023-04-10 AC energy saver V6
2023-04-10 added schematic pdf
2023-05-27 Add apps directory tree
2023-05-27 Add ios app directory tree
2023-05-27 Initial commit
    - Add dependencies
    - Add UI screens
2023-05-27 Update libraries
2023-05-28 Add screen: AddDeviceManually
2023-05-29 Add screen: IrCodeSetupScreen
2023-05-29 Add VM event
2023-05-29 Update email
2023-05-30 Adding V7 of the PCB
2023-05-31 Handle permissions
2023-06-02 [doc] BLE Protocol definition document. Initial version
2023-06-02 Added requirements document
    Each requirement has a corresponding:
    - BLE protocol
    - Comments
    - Questions
2023-06-03 Add manual motion detection controller
2023-06-07 Add TriggerSetupScreen
2023-06-07 Rename IMotionDevice to MotionDeviceListEntry
2023-06-07 Add DeviceOverviewScreen
2023-06-07 Add IrCodesOverviewScreen
2023-06-07 Update IrCodeSetupScreen
2023-06-07 Add devices and ircodes repos
2023-06-08 Rename
2023-06-08 Add DI: Hilt
2023-06-09 Add Navigation logic
2023-06-09 Cleaner Navigation logic
2023-06-09 Add IrCodesOverviewNavigation
2023-06-15 Add BLE protocol specifications
2023-06-16 Updating to the latest V7 PCB that was submitted to JLCPCB
2023-07-06 Adding the toolchain for building the firmware on MacOS. This toolchain should work for Intel Macs and Apple Silicon Macs (using Rosetta 2).
2023-07-06 Firmware changes for the latest hardware version, which is V7. Fixing the make system so that it builds on MacOS using the supplied toolchain.
2023-07-08 Added eclipse project for easier development and debug
2023-07-08 [ble] Custom device protocol first drop
2023-07-10 [ble] Removed legacy custom characteristics
2023-11-13 [ble] Custom protocol demo data report
2023-12-23 Update README.md
    Update protocol with more examples
    Trigger commands are not sent as UTF8 Strings
2024-01-11 Update README.md
    Add req.1.14
